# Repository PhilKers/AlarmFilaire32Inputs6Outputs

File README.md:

# Centrale d'alarme filaire 32 zones / 6 sorties — STM32H7

Conception complète (matériel + logiciel) d'une centrale d'alarme :

- **32 entrées filaires** supervisées : NF, NO, simple ou double résistance de fin de ligne (repos / alarme / coupure / court-circuit)
- **6 sorties relais**, mode électrique **configurable par logiciel** : contact sec, +12 V ou +5 V
- **Annonces vocales** en français (haut-parleur local et messages au téléphone)
- **Ethernet** : API HTTP/JSON, mise à l'heure SNTP
- **4G** (SIMCom A7670E + micro-SIM) : SMS, appels en cascade, acquittement et commandes DTMF, pilotage par SMS
- **Alimentation secourue** : bloc 13,8 V avec chargeur, batterie 12 V, surveillance secteur / batterie / fusibles
- **Écran tactile 10,4" 1024×768** (LVGL v9)
- **MCU STM32H743BIT6** (Cortex-M7 480 MHz) + SDRAM 32 Mo + Flash QSPI 16 Mo + microSD

## Documentation

| Document | Contenu |
|---|---|
| [docs/01-architecture.md](docs/01-architecture.md) | Synoptique, choix techniques, bilan de consommation, autonomie |
| [docs/02-schema-electrique.md](docs/02-schema-electrique.md) | Schéma détaillé par feuillets : alimentation, MCU, mémoires, écran, zones, relais, audio, Ethernet, 4G, connecteurs |
| [docs/03-brochage-stm32.md](docs/03-brochage-stm32.md) | Affectation de toutes les broches du STM32 |
| [docs/04-nomenclature.md](docs/04-nomenclature.md) | Nomenclature (BOM) |
| [docs/05-logiciel.md](docs/05-logiciel.md) | Architecture logicielle, machine d'états, tâches, commandes SMS/DTMF/API, construction |
| [docs/06-mise-en-service.md](docs/06-mise-en-service.md) | Câblage des détecteurs, programmation, procès-verbal d'essais |
| [hardware/kicad/LISEZMOI.md](hardware/kicad/LISEZMOI.md) | **Projet KiCad** : schéma (9 feuillets), circuit imprimé placé (4 couches, 300 × 210 mm), PDF |
| [hardware/netlist/LISEZMOI.md](hardware/netlist/LISEZMOI.md) | **Netlist pour OrCAD** (Allegro/PCB Editor et OrCAD PCB II), nomenclature et empreintes générées |

## Arborescence

```
firmware/
├── core/                 Noyau portable en C11 (logique d'alarme), testé sur PC
├── platform/stm32h7/     Pilotes et tâches FreeRTOS pour la carte (HAL, lwIP, LVGL, FatFS)
├── tests/                Tests unitaires du noyau
├── sim/                  Simulateur console
└── CMakeLists.txt        Construction PC (tests + simulateur)
tools/
├── gen_voix.sh           Génération des messages vocaux (WAV + AMR)
└── gen_fonts.sh          Génération des polices LVGL avec accents
```

## Essai rapide sur PC

```bash
cd firmware
cmake -S . -B build && cmake --build build
./build/test_core      # tests unitaires du noyau
./build/alarm_sim      # simulateur : essayez « mes 1234 », « att 31 », « z 3 ouvert », « sms 1234 ETAT »
```

## État du projet

| Partie | État |
|---|---|
| Schéma de référence, brochage, nomenclature | Rédigés — brochage à valider dans STM32CubeMX |
| Netlist (587 composants, 466 équipotentielles) | Générée et vérifiée automatiquement (brochages issus de bibliothèques KiCad) |
| Schéma KiCad (9 feuillets) + PDF | Généré depuis la même description, relu et validé par KiCad (connectivité identique) |
| Circuit imprimé KiCad | Placé, **routage partiel** (251 équipotentielles, vias de masse) ; DRC sans erreur ; alimentations et liaisons critiques à router à la main |
| Noyau logiciel (zones, moteur, sorties, codes, journal, notifications, voix, commandes) | Écrit, **compilé et testé** (105 vérifications) |
| Couche STM32 (pilotes, modem 4G, réseau, IHM) | Écrite, **non compilée ni essayée sur carte** (nécessite le projet CubeMX) |
| Prototype matériel | À réaliser |

> Projet personnel non certifié NF&A2P / EN 50131. La partie 230 V est confiée à un bloc d'alimentation du commerce et doit être raccordée par une personne qualifiée.

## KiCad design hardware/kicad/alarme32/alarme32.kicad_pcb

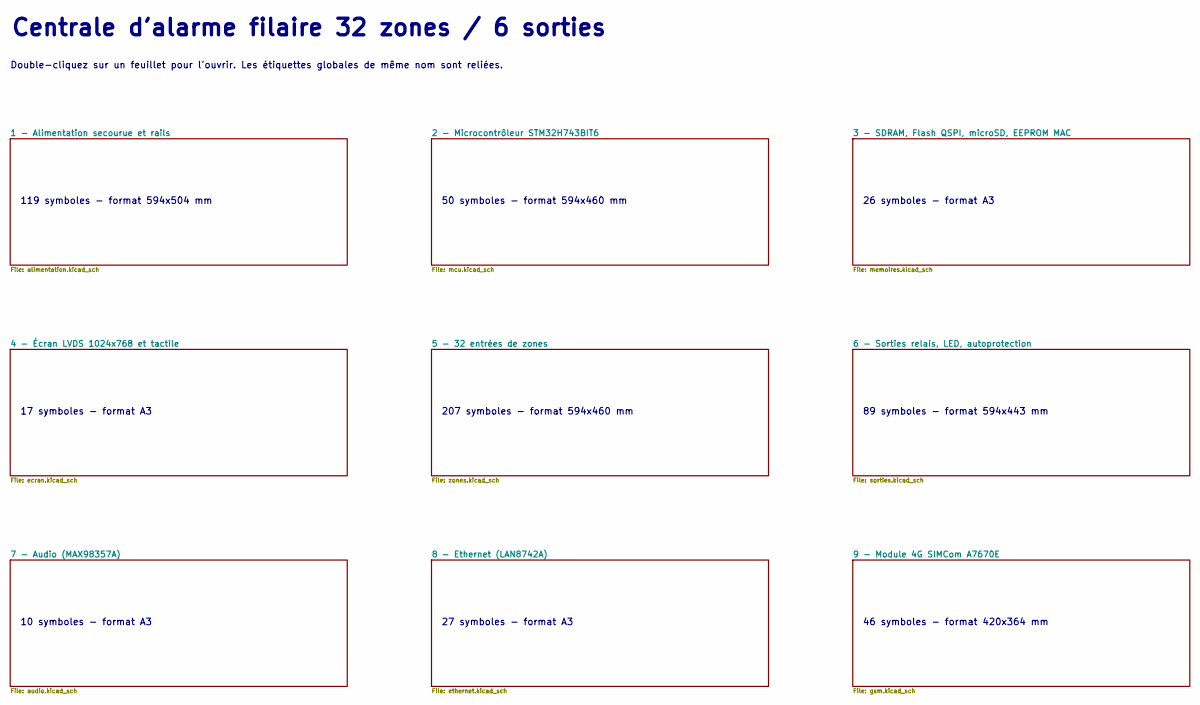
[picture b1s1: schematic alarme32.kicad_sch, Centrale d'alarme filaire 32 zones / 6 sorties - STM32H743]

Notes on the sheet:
Centrale d'alarme filaire 32 zones / 6 sorties
Double-cliquez sur un feuillet pour l'ouvrir. Les étiquettes globales de même nom sont reliées.
119 symboles - format 594x504 mm
50 symboles - format 594x460 mm
26 symboles - format A3
17 symboles - format A3
207 symboles - format 594x460 mm
89 symboles - format 594x443 mm
10 symboles - format A3
27 symboles - format A3
46 symboles - format 420x364 mm

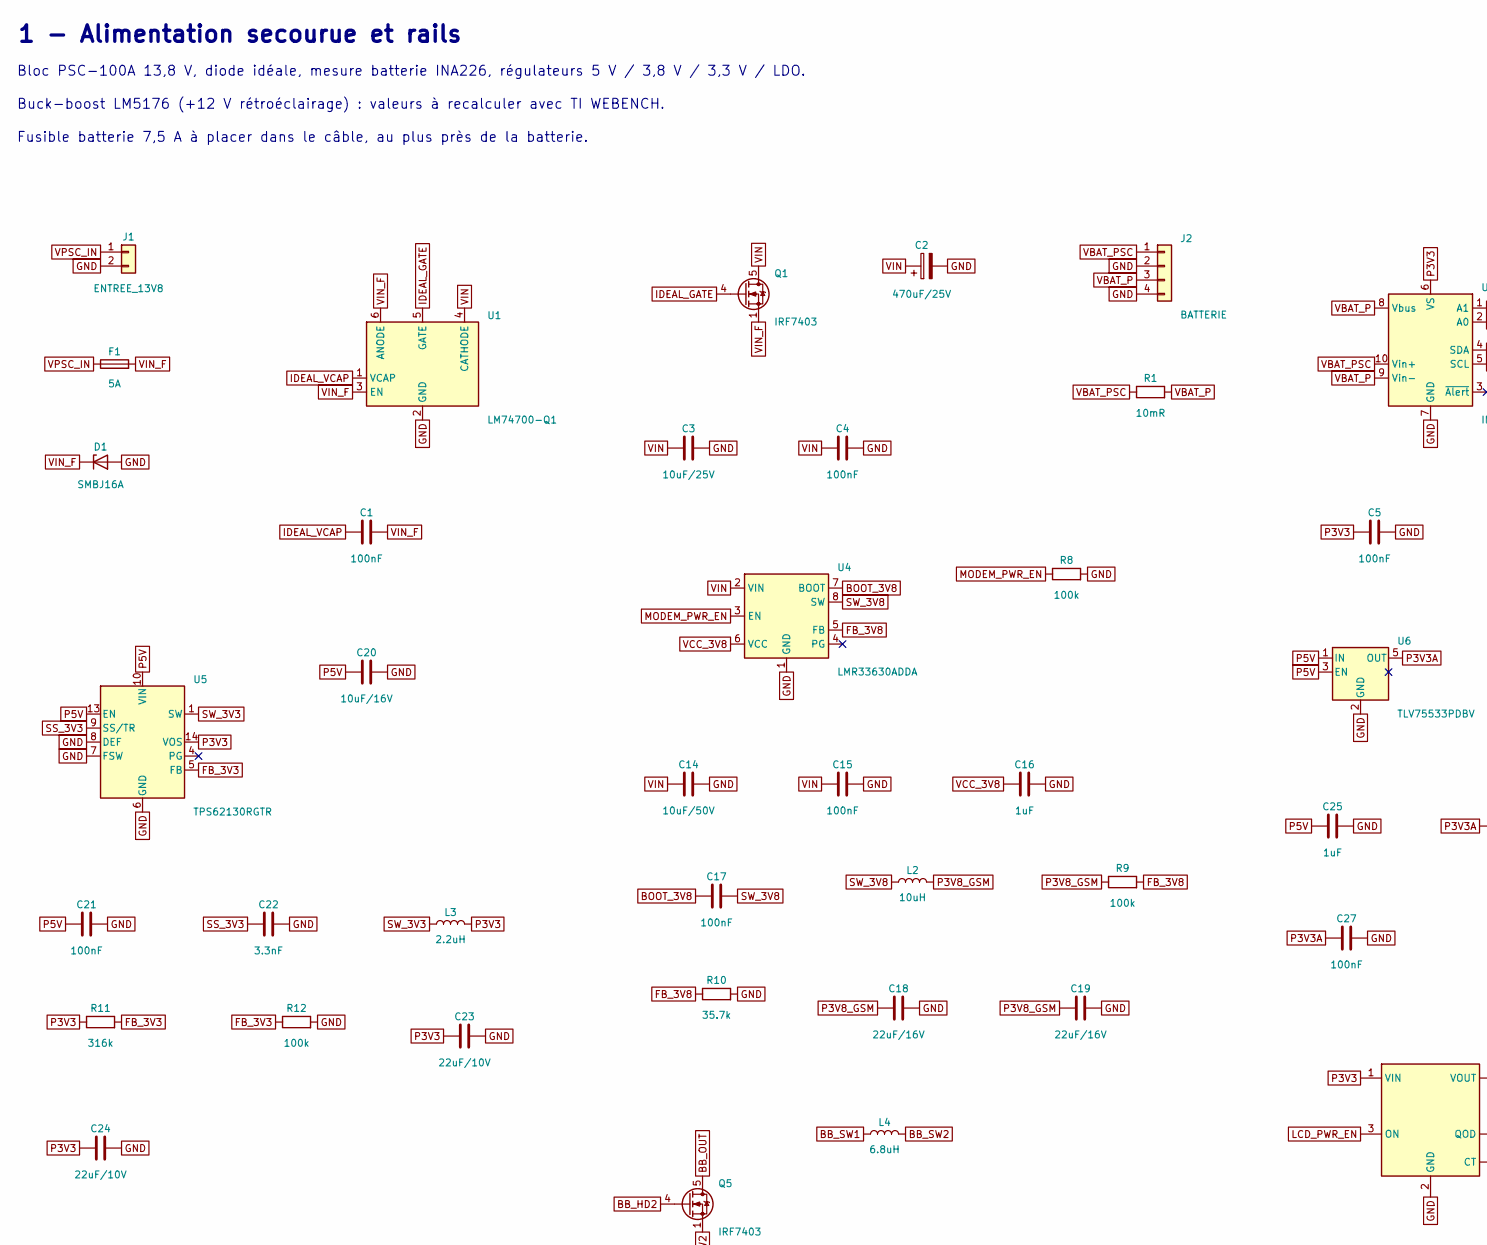
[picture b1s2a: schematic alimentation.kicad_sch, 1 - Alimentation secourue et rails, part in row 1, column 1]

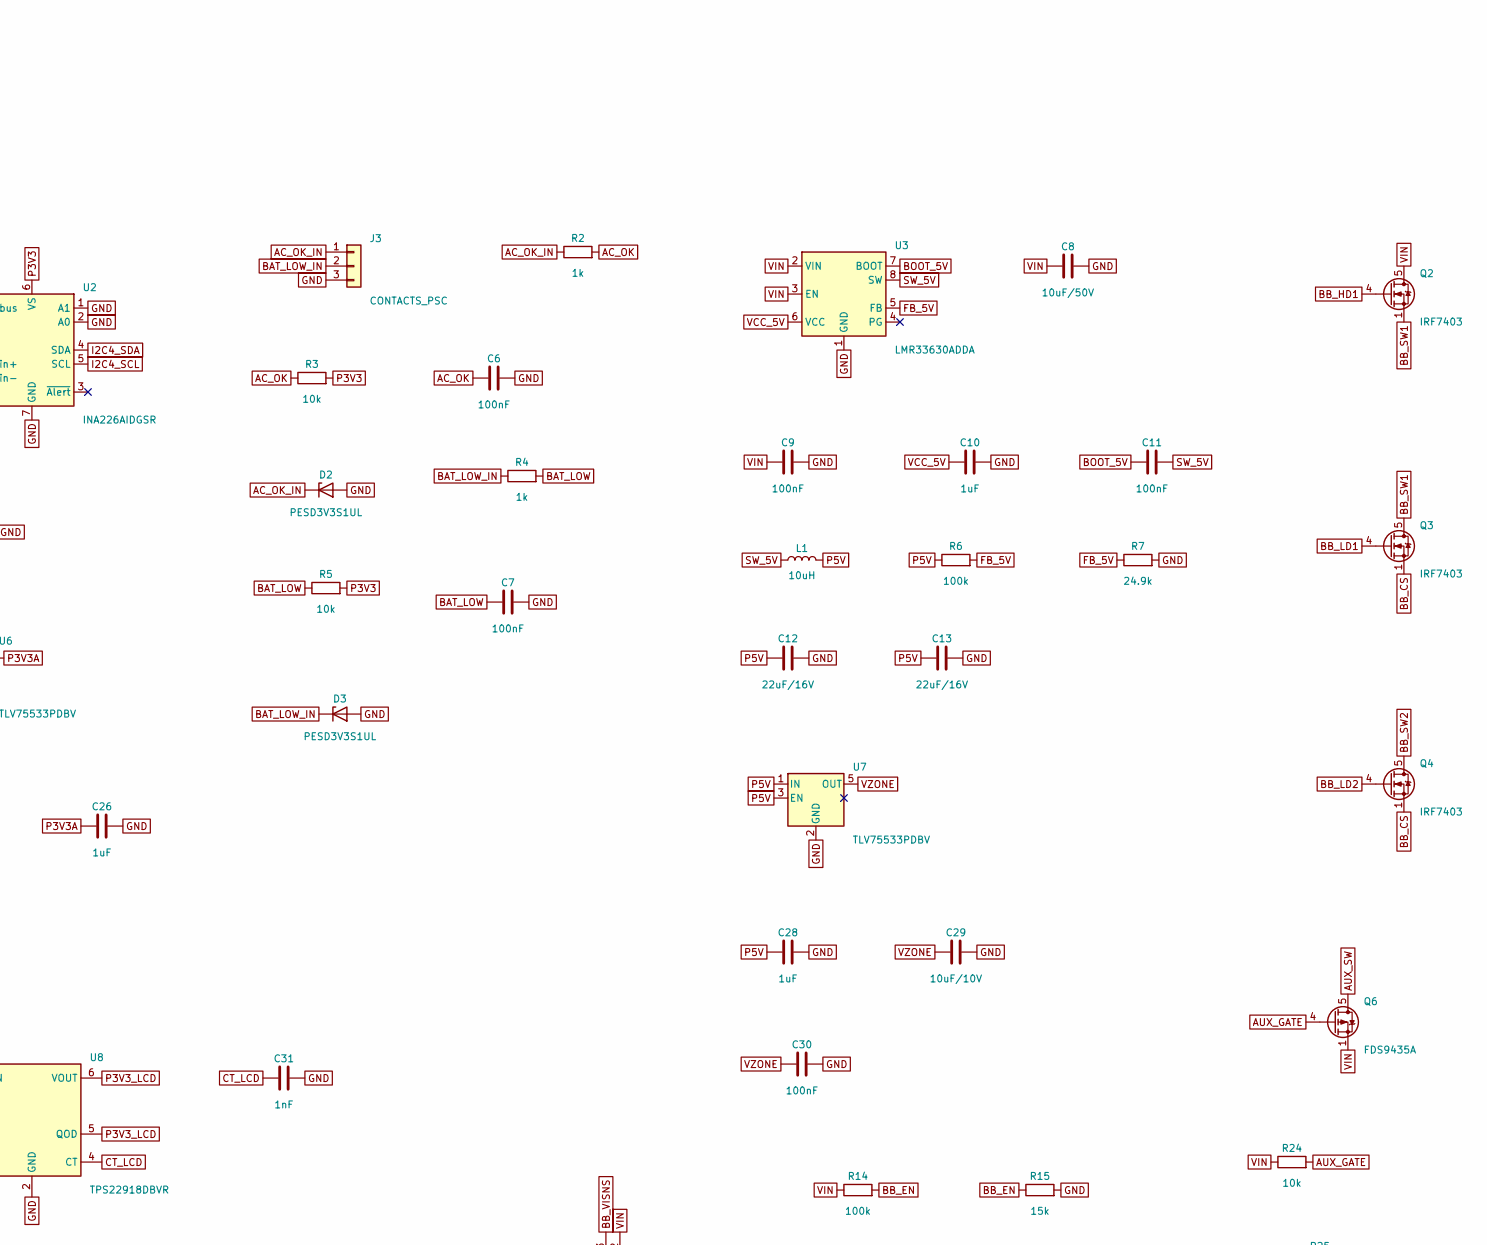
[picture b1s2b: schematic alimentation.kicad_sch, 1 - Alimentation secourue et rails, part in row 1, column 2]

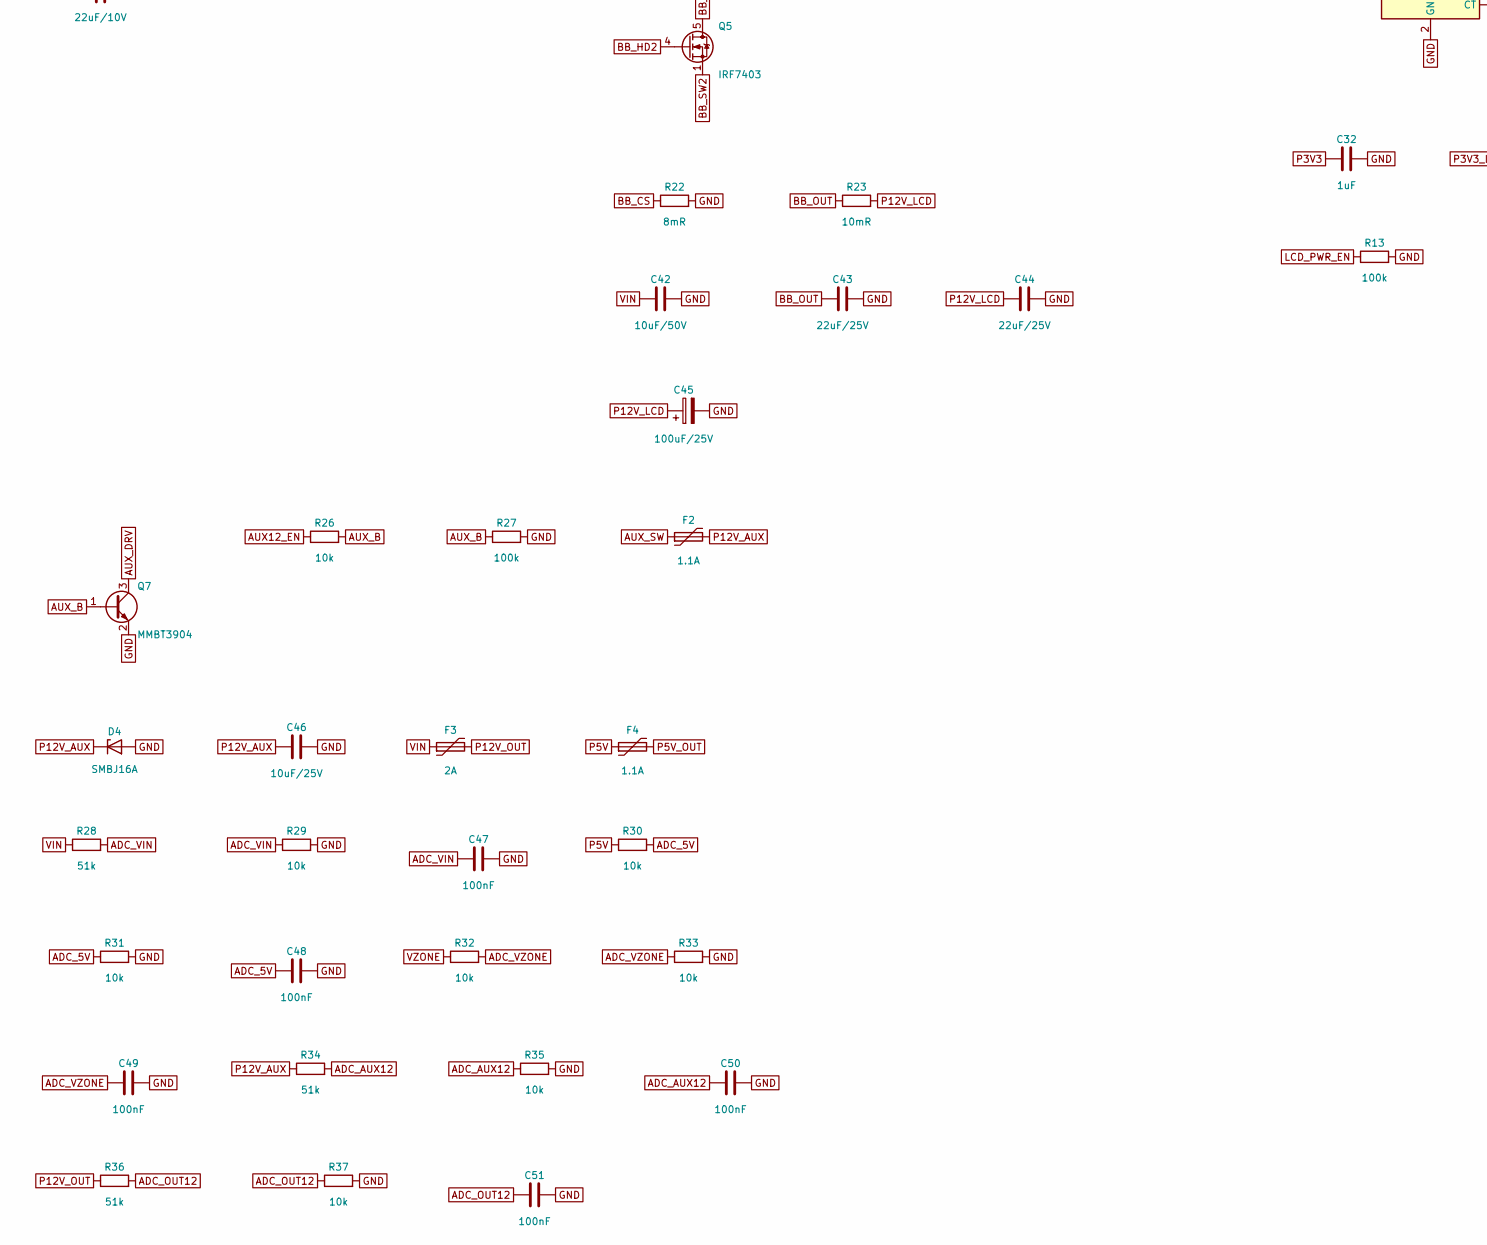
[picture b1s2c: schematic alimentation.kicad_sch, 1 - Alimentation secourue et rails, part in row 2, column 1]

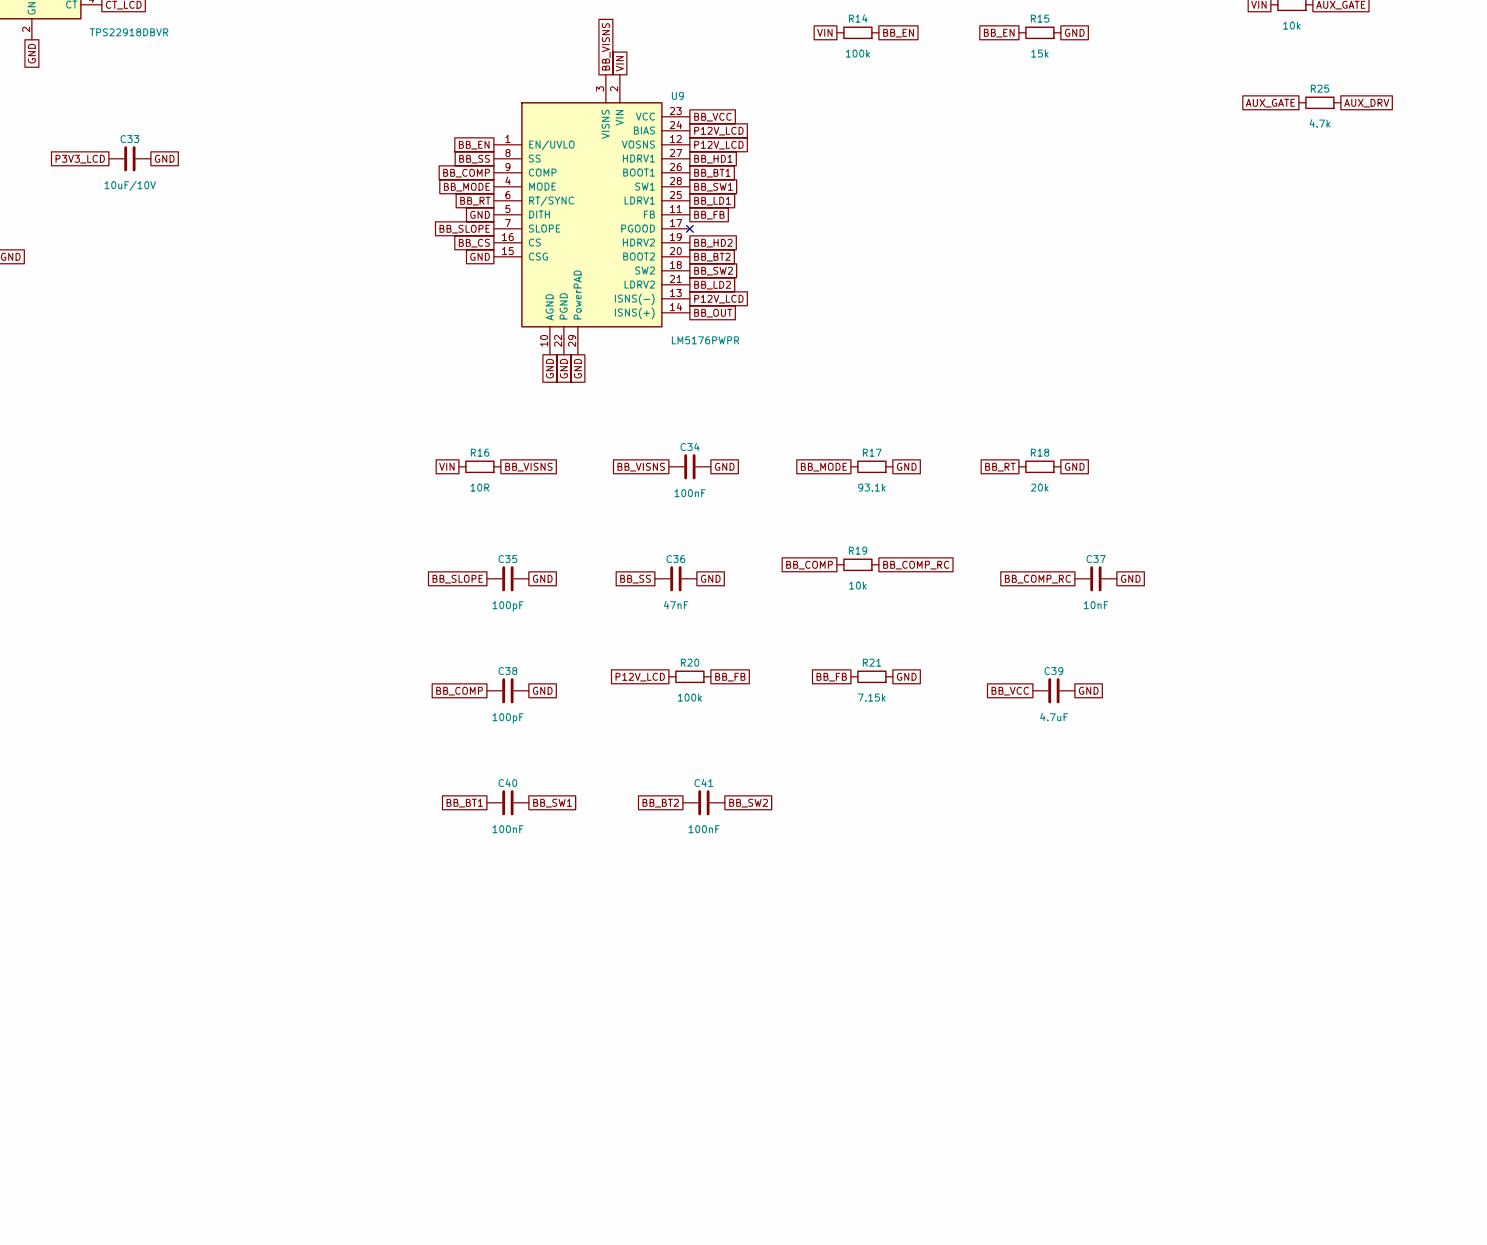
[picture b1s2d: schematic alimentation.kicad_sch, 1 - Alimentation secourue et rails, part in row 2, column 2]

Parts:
C1, C4, C5, C6, C7, C9, C11, C15, C17, C21, C27, C30, C34, C40, C41, C47, C48, C49, C50, C51: 100nF; C_0603_1608Metric
C2: 470uF/25V; CP_Elec_10x10.5
C3, C46: 10uF/25V; C_1210_3225Metric
C8, C14, C42: 10uF/50V; C_1210_3225Metric
C10, C16, C25, C26, C28, C32: 1uF; C_0603_1608Metric
C12, C13, C18, C19: 22uF/16V; C_1210_3225Metric
C20: 10uF/16V; C_0805_2012Metric
C22: 3.3nF; C_0603_1608Metric
C23, C24: 22uF/10V; C_0805_2012Metric
C29, C33: 10uF/10V; C_0805_2012Metric
C31: 1nF; C_0603_1608Metric
C35, C38: 100pF; C_0603_1608Metric
C36: 47nF; C_0603_1608Metric
C37: 10nF; C_0603_1608Metric
C39: 4.7uF; C_0603_1608Metric
C43, C44: 22uF/25V; C_1210_3225Metric
C45: 100uF/25V; CP_Elec_8x10
D1, D4: SMBJ16A; D_SMB
D2, D3: PESD3V3S1UL; D_SOD-323
F1: 5A; Fuseholder_Littelfuse_Nano2_154x
F2, F4: 1.1A; Fuse_1812_4532Metric
F3: 2A; Fuse_1812_4532Metric
J1: ENTREE_13V8; TerminalBlock_Phoenix_MKDS-1,5-2-5.08_1x02_P5.08mm_Horizont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
J2: BATTERIE; TerminalBlock_Phoenix_MKDS-1,5-4-5.08_1x04_P5.08mm_Horizont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
J3: CONTACTS_PSC; TerminalBlock_Phoenix_MKDS-1,5-3-5.08_1x03_P5.08mm_Horizont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
L1, L2: 10uH; L_Coilcraft_XAL6060-XXX
L3: 2.2uH; L_Coilcraft_XxL4020
L4: 6.8uH; L_Coilcraft_XAL6060-XXX
Q1, Q2, Q3, Q4, Q5: IRF7403; SOIC-8_3.9x4.9mm_P1.27mm
Q6: FDS9435A; SOIC-8_3.9x4.9mm_P1.27mm
Q7: MMBT3904; SOT-23
R1: 10mR; R_2512_6332Metric
R2, R4: 1k; R_0603_1608Metric
R3, R5, R19, R24, R26, R29, R30, R31, R32, R33, R35, R37: 10k; R_0603_1608Metric
R6, R8, R9, R12, R13, R14, R20, R27: 100k; R_0603_1608Metric
R7: 24.9k; R_0603_1608Metric
R10: 35.7k; R_0603_1608Metric
R11: 316k; R_0603_1608Metric
R15: 15k; R_0603_1608Metric
R16: 10R; R_0603_1608Metric
R17: 93.1k; R_0603_1608Metric
R18: 20k; R_0603_1608Metric
R21: 7.15k; R_0603_1608Metric
R22: 8mR; R_1206_3216Metric
R23: 10mR; R_1206_3216Metric
R25: 4.7k; R_0603_1608Metric
R28, R34, R36: 51k; R_0603_1608Metric
U1: LM74700-Q1; SOT-23-6
U2: INA226AIDGSR; VSSOP-10_3x3mm_P0.5mm
U3, U4: LMR33630ADDA; TI_SO-PowerPAD-8_ThermalVias
U5: TPS62130RGTR; VQFN-16-1EP_3x3mm_P0.5mm_EP1.68x1.68mm_ThermalVias
U6, U7: TLV75533PDBV; SOT-23-5
U8: TPS22918DBVR; SOT-23-6
U9: LM5176PWPR; HTSSOP-28-1EP_4.4x9.7mm_P0.65mm_EP2.85x5.4mm_ThermalVias

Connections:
AC_OK: C6.1, R2.2, R3.1; also elsewhere on the board
AC_OK_IN: D2.1 (K), J3.1, R2.1
ADC_5V: C48.1, R30.2, R31.1; also elsewhere on the board
ADC_AUX12: C50.1, R34.2, R35.1; also elsewhere on the board
ADC_OUT12: C51.1, R36.2, R37.1; also elsewhere on the board
ADC_VIN: C47.1, R28.2, R29.1; also elsewhere on the board
ADC_VZONE: C49.1, R32.2, R33.1; also elsewhere on the board
AUX12_EN: R26.1; also elsewhere on the board
AUX_B: Q7.1 (B), R26.2, R27.1
AUX_DRV: Q7.3 (C), R25.2
AUX_GATE: Q6.4 (G), R24.2, R25.1
AUX_SW: F2.1, Q6.5 (D), Q6.6 (D), Q6.7 (D), Q6.8 (D)
BAT_LOW: C7.1, R4.2, R5.1; also elsewhere on the board
BAT_LOW_IN: D3.1 (K), J3.2, R4.1
BB_BT1: C40.1, U9.26 (BOOT1)
BB_BT2: C41.1, U9.20 (BOOT2)
BB_COMP: C38.1, R19.1, U9.9 (COMP)
BB_COMP_RC: C37.1, R19.2
BB_CS: Q3.1 (S), Q3.2 (S), Q3.3 (S), Q4.1 (S), Q4.2 (S), Q4.3 (S), R22.1, U9.16 (CS)
BB_EN: R14.2, R15.1, U9.1 (EN/UVLO)
BB_FB: R20.2, R21.1, U9.11 (FB)
BB_HD1: Q2.4 (G), U9.27 (HDRV1)
BB_HD2: Q5.4 (G), U9.19 (HDRV2)
BB_LD1: Q3.4 (G), U9.25 (LDRV1)
BB_LD2: Q4.4 (G), U9.21 (LDRV2)
BB_MODE: R17.1, U9.4 (MODE)
BB_OUT: C43.1, Q5.5 (D), Q5.6 (D), Q5.7 (D), Q5.8 (D), R23.1, U9.14 (ISNS(+))
BB_RT: R18.1, U9.6 (RT/SYNC)
BB_SLOPE: C35.1, U9.7 (SLOPE)
BB_SS: C36.1, U9.8 (SS)
BB_SW1: C40.2, L4.1, Q2.1 (S), Q2.2 (S), Q2.3 (S), Q3.5 (D), Q3.6 (D), Q3.7 (D), Q3.8 (D), U9.28 (SW1)
BB_SW2: C41.2, L4.2, Q4.5 (D), Q4.6 (D), Q4.7 (D), Q4.8 (D), Q5.1 (S), Q5.2 (S), Q5.3 (S), U9.18 (SW2)
BB_VCC: C39.1, U9.23 (VCC)
BB_VISNS: C34.1, R16.2, U9.3 (VISNS)
BOOT_3V8: C17.1, U4.7 (BOOT)
BOOT_5V: C11.1, U3.7 (BOOT)
CT_LCD: C31.1, U8.4 (CT)
FB_3V3: R11.2, R12.1, U5.5 (FB)
FB_3V8: R9.2, R10.1, U4.5 (FB)
FB_5V: R6.2, R7.1, U3.5 (FB)
GND: C2.2, C3.2, C4.2, C5.2, C6.2, C7.2, C8.2, C9.2, C10.2, C12.2, C13.2, C14.2, C15.2, C16.2, C18.2, C19.2, C20.2, C21.2, C22.2, C23.2, C24.2, C25.2, C26.2, C27.2, C28.2, C29.2, C30.2, C31.2, C32.2, C33.2, C34.2, C35.2, C36.2, C37.2, C38.2, C39.2, C42.2, C43.2, C44.2, C45.2, C46.2, C47.2, C48.2, C49.2, C50.2, C51.2, D1.2 (A), D2.2 (A), D3.2 (A), D4.2 (A), J1.2, J2.2, J2.4, J3.3, Q7.2 (E), R7.2, R8.2, R10.2, R12.2, R13.2, R15.2, R17.2, R18.2, R21.2, R22.2, R27.2, R29.2, R31.2, R33.2, R35.2, R37.2, U1.2 (GND), U2.1 (A1), U2.2 (A0), U2.7 (GND), U3.1 (GND), U3.9 (GND), U4.1 (GND), U4.9 (GND), U5.6 (GND), U5.7 (FSW), U5.8 (DEF), U5.15 (GND), U5.16 (GND), U5.17 (GND), U6.2 (GND), U7.2 (GND), U8.2 (GND), U9.5 (DITH), U9.10 (AGND), U9.15 (CSG), U9.22 (PGND), U9.29 (PowerPAD); also elsewhere on the board
I2C4_SCL: U2.5 (SCL); also elsewhere on the board
I2C4_SDA: U2.4 (SDA); also elsewhere on the board
IDEAL_GATE: Q1.4 (G), U1.5 (GATE)
IDEAL_VCAP: C1.1, U1.1 (VCAP)
LCD_PWR_EN: R13.1, U8.3 (ON); also elsewhere on the board
MODEM_PWR_EN: R8.1, U4.3 (EN); also elsewhere on the board
P3V3: C5.1, C23.1, C24.1, C32.1, L3.2, R3.2, R5.2, R11.1, U2.6 (VS), U5.14 (VOS), U8.1 (VIN); also elsewhere on the board
P3V3A: C26.1, C27.1, U6.5 (OUT); also elsewhere on the board
P3V3_LCD: C33.1, U8.5 (QOD), U8.6 (VOUT); also elsewhere on the board
P3V8_GSM: C18.1, C19.1, L2.2, R9.1; also elsewhere on the board
P5V: C12.1, C13.1, C20.1, C21.1, C25.1, C28.1, F4.1, L1.2, R6.1, R30.1, U5.10 (VIN), U5.11 (VIN), U5.12 (VIN), U5.13 (EN), U6.1 (IN), U6.3 (EN), U7.1 (IN), U7.3 (EN); also elsewhere on the board
P5V_OUT: F4.2; also elsewhere on the board
P12V_AUX: C46.1, D4.1 (K), F2.2, R34.1; also elsewhere on the board
P12V_LCD: C44.1, C45.1, R20.1, R23.2, U9.12 (VOSNS), U9.13 (ISNS(-)), U9.24 (BIAS); also elsewhere on the board
P12V_OUT: F3.2, R36.1; also elsewhere on the board
SS_3V3: C22.1, U5.9 (SS/TR)
SW_3V3: L3.1, U5.1 (SW), U5.2 (SW), U5.3 (SW)
SW_3V8: C17.2, L2.1, U4.8 (SW)
SW_5V: C11.2, L1.1, U3.8 (SW)
VBAT_P: J2.3, R1.2, U2.8 (Vbus), U2.9 (Vin-)
VBAT_PSC: J2.1, R1.1, U2.10 (Vin+)
VCC_3V8: C16.1, U4.6 (VCC)
VCC_5V: C10.1, U3.6 (VCC)
VIN: C2.1, C3.1, C4.1, C8.1, C9.1, C14.1, C15.1, C42.1, F3.1, Q1.5 (D), Q1.6 (D), Q1.7 (D), Q1.8 (D), Q2.5 (D), Q2.6 (D), Q2.7 (D), Q2.8 (D), Q6.1 (S), Q6.2 (S), Q6.3 (S), R14.1, R16.1, R24.1, R28.1, U1.4 (CATHODE), U3.2 (VIN), U3.3 (EN), U4.2 (VIN), U9.2 (VIN); also elsewhere on the board
VIN_F: C1.2, D1.1 (K), F1.2, Q1.1 (S), Q1.2 (S), Q1.3 (S), U1.3 (EN), U1.6 (ANODE)
VPSC_IN: F1.1, J1.1
VZONE: C29.1, C30.1, R32.1, U7.5 (OUT); also elsewhere on the board

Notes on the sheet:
1 - Alimentation secourue et rails
Bloc PSC-100A 13,8 V, diode idéale, mesure batterie INA226, régulateurs 5 V / 3,8 V / 3,3 V / LDO.
Buck-boost LM5176 (+12 V rétroéclairage) : valeurs à recalculer avec TI WEBENCH.
Fusible batterie 7,5 A à placer dans le câble, au plus près de la batterie.
